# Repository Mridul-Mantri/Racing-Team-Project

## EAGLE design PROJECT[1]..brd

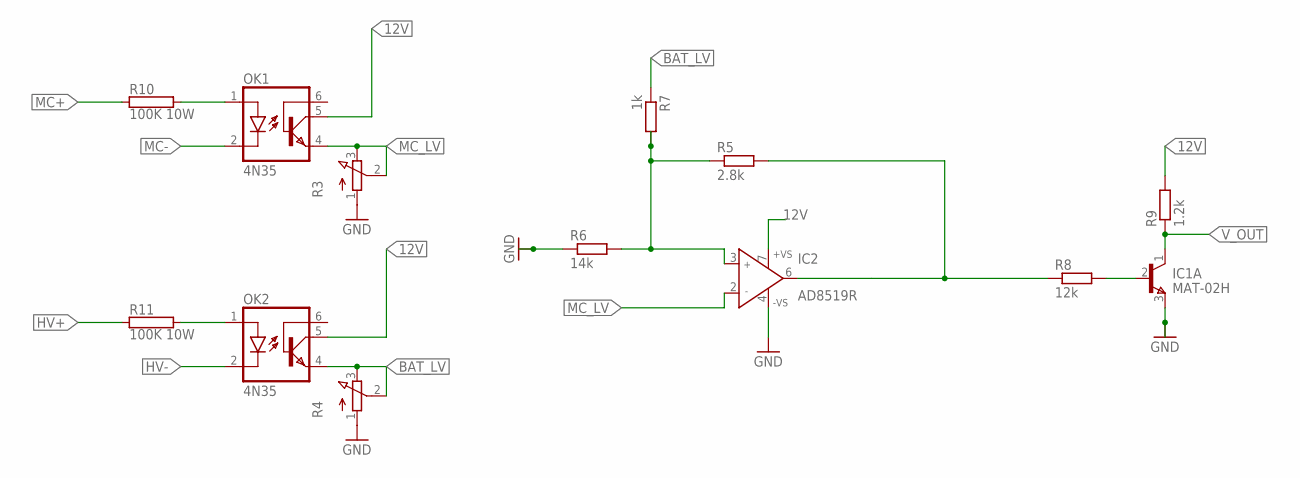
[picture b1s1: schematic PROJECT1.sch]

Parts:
IC1: MAT-02H; TO78
IC2: AD8519R; SO8
OK1, OK2: 4N35; DIL06
R3, R4: 3RP/1610N
R5: 2.8k; 0207/10
R6: 14k; 0207/10
R7: 1k; 0207/10
R8: 12k; 0207/10
R9: 1.2k; 0207/10
R10, R11: 100K 10W; TO-247-2V

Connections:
12V: IC2.7 (+VS), OK1.5 (COL), OK2.5 (COL), R9.2
BAT_LV: OK2.4 (EMI), R4.2 (S), R4.3 (E), R7.1
GND: IC1.3 (E), IC2.4 (-VS), R3.1 (A), R4.1 (A), R6.1
HV+: R11.1
HV-: OK2.2 (C)
MC+: R10.1
MC-: OK1.2 (C)
MC_LV: IC2.2 (IN-), OK1.4 (EMI), R3.2 (S), R3.3 (E)
unnamed: OK1.1 (A), R10.2
unnamed: OK2.1 (A), R11.2
unnamed: IC2.3 (IN+), R5.1, R6.2, R7.2
unnamed: IC2.6 (OUT), R5.2, R8.1
unnamed: IC1.2 (B), R8.2
V_OUT: IC1.1 (C), R9.1

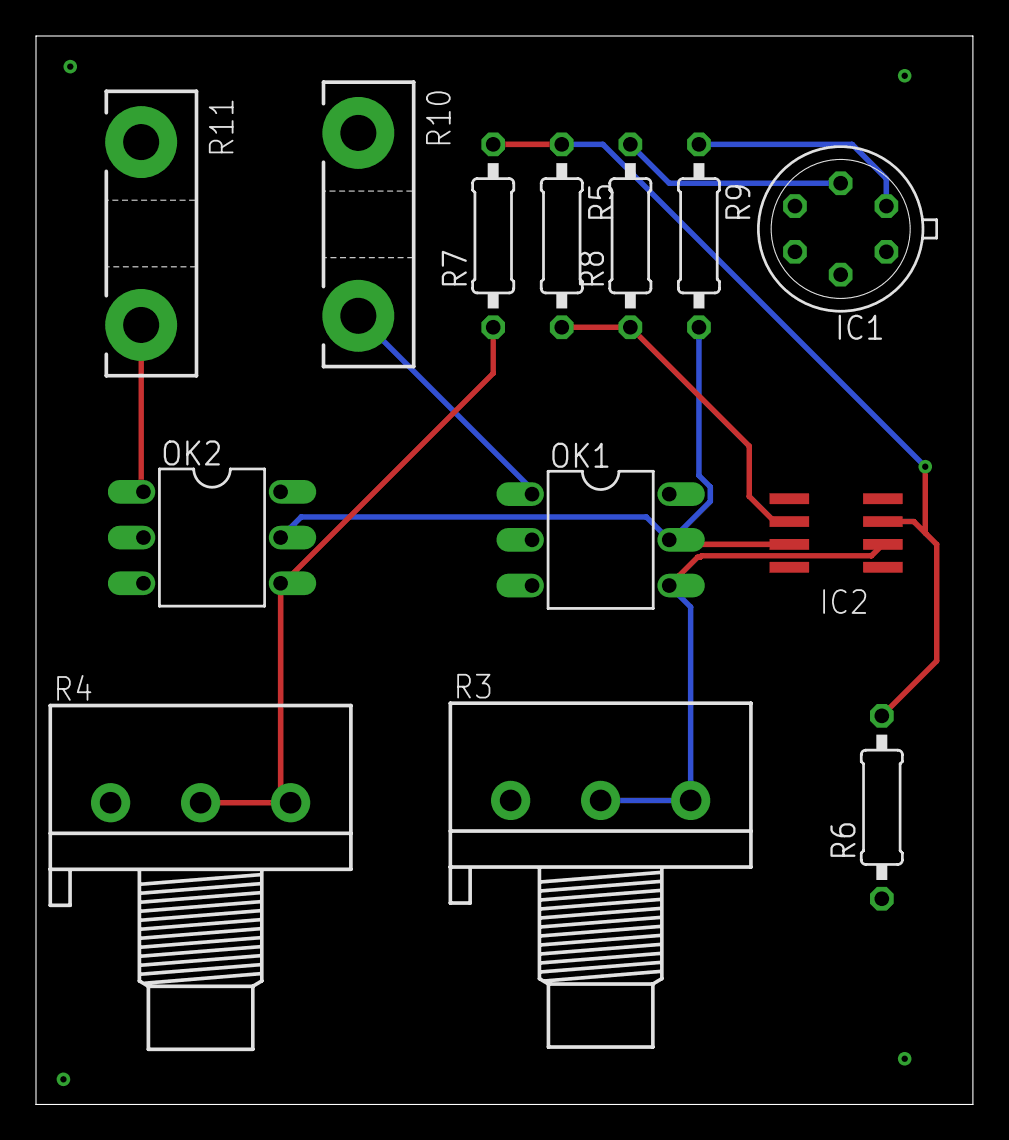
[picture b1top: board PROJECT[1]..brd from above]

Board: 2 copper layers, 52.1 x 59.4 mm, 13 parts (0 on the bottom side), 10 nets.
